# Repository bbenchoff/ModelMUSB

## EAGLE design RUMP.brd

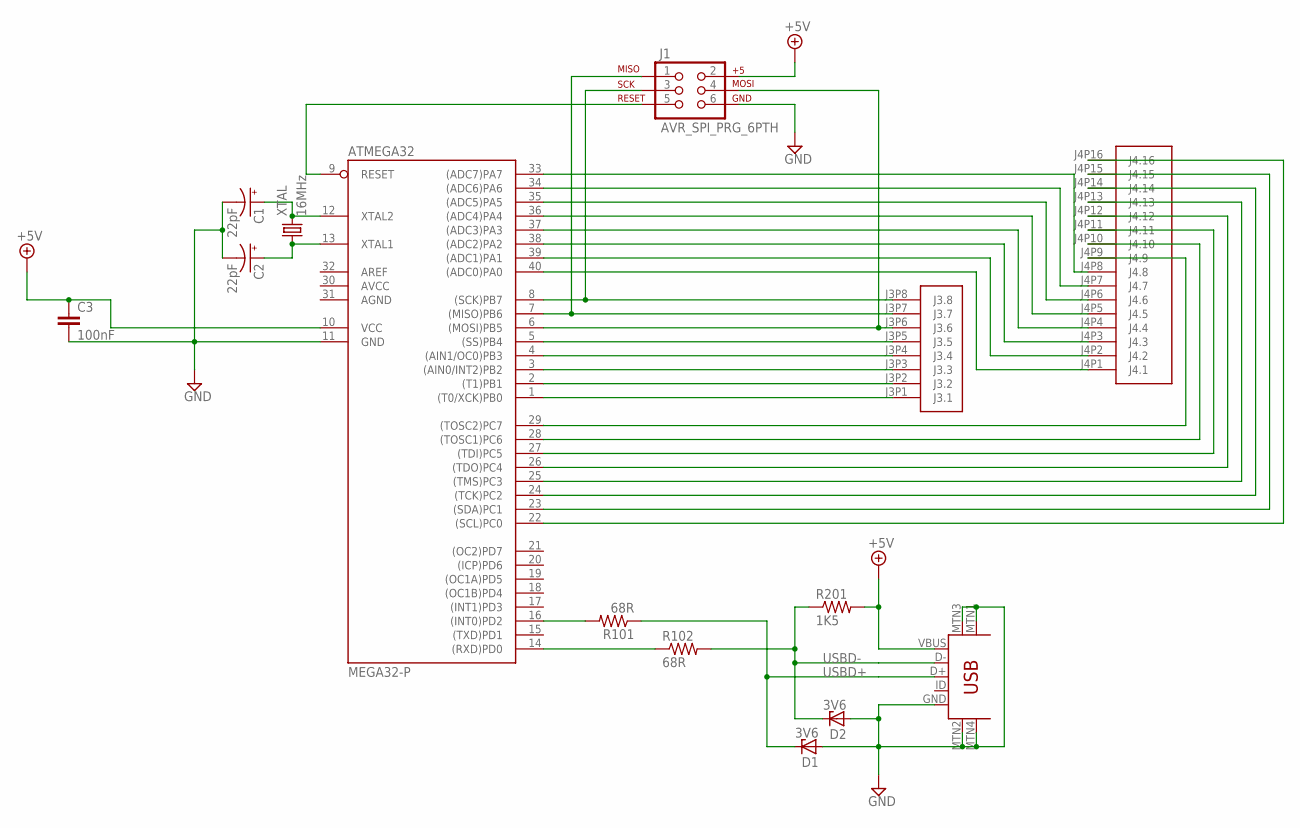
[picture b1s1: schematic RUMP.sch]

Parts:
ATMEGA32: MEGA32-P; DIL40
C1, C2: 22pF; E2-4
C3: 100nF; C2.5-2
D1, D2: 3V6; DO35Z10
J1: AVR_SPI_PRG_6PTH; 2X3
R101, R102: 68R; 0204/7
R201: 1K5; 0204/7
U$1: MODEL-M-J3
U$2: MODEL-M-J4
U$3: USB-MINIB-5PIN; USB-MINIB
XTAL: 16MHz; HC49/S

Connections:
+5V: ATMEGA32.10 (VCC), C3.1, J1.2, R201.2, U$3.VBUS
AGND: ATMEGA32.31 (AGND)
AVCC: ATMEGA32.30 (AVCC)
GND: ATMEGA32.11 (GND), C1.-, C2.-, C3.2, D1.A, D2.A, J1.6, U$3.GND, U$3.MTN1 (MTN2), U$3.MTN2 (MTN3), U$3.MTN3 (MTN1), U$3.MTN4
unnamed: ATMEGA32.14 ((RXD)PD0), R102.1
unnamed: ATMEGA32.16 ((INT0)PD2), R101.2
unnamed: ATMEGA32.1 ((T0/XCK)PB0), U$1.J3P1 (J3.1)
unnamed: ATMEGA32.2 ((T1)PB1), U$1.J3P2 (J3.2)
unnamed: ATMEGA32.3 ((AIN0/INT2)PB2), U$1.J3P3 (J3.3)
unnamed: ATMEGA32.4 ((AIN1/OC0)PB3), U$1.J3P4 (J3.4)
unnamed: ATMEGA32.5 ((SS)PB4), U$1.J3P5 (J3.5)
unnamed: ATMEGA32.6 ((MOSI)PB5), J1.4, U$1.J3P6 (J3.6)
unnamed: ATMEGA32.7 ((MISO)PB6), J1.1, U$1.J3P7 (J3.7)
unnamed: ATMEGA32.8 ((SCK)PB7), J1.3, U$1.J3P8 (J3.8)
unnamed: ATMEGA32.40 ((ADC0)PA0), U$2.J4P1 (J4.1)
unnamed: ATMEGA32.39 ((ADC1)PA1), U$2.J4P2 (J4.2)
unnamed: ATMEGA32.38 ((ADC2)PA2), U$2.J4P3 (J4.3)
unnamed: ATMEGA32.37 ((ADC3)PA3), U$2.J4P4 (J4.4)
unnamed: ATMEGA32.36 ((ADC4)PA4), U$2.J4P5 (J4.5)
unnamed: ATMEGA32.35 ((ADC5)PA5), U$2.J4P6 (J4.6)
unnamed: ATMEGA32.34 ((ADC6)PA6), U$2.J4P7 (J4.7)
unnamed: ATMEGA32.33 ((ADC7)PA7), U$2.J4P8 (J4.8)
unnamed: ATMEGA32.12 (XTAL2), C1.+, XTAL.2
unnamed: ATMEGA32.13 (XTAL1), C2.+, XTAL.1
unnamed: ATMEGA32.29 ((TOSC2)PC7), U$2.J4P9 (J4.9)
unnamed: ATMEGA32.28 ((TOSC1)PC6), U$2.J4P10 (J4.10)
unnamed: ATMEGA32.27 ((TDI)PC5), U$2.J4P11 (J4.11)
unnamed: ATMEGA32.26 ((TDO)PC4), U$2.J4P12 (J4.12)
unnamed: ATMEGA32.25 ((TMS)PC3), U$2.J4P13 (J4.13)
unnamed: ATMEGA32.24 ((TCK)PC2), U$2.J4P14 (J4.14)
unnamed: ATMEGA32.23 ((SDA)PC1), U$2.J4P15 (J4.15)
unnamed: ATMEGA32.22 ((SCL)PC0), U$2.J4P16 (J4.16)
RESET: ATMEGA32.9 (RESET), J1.5
USBD+: D1.C, R101.1, U$3.D+
USBD-: D2.C, R102.2, R201.1, U$3.D-

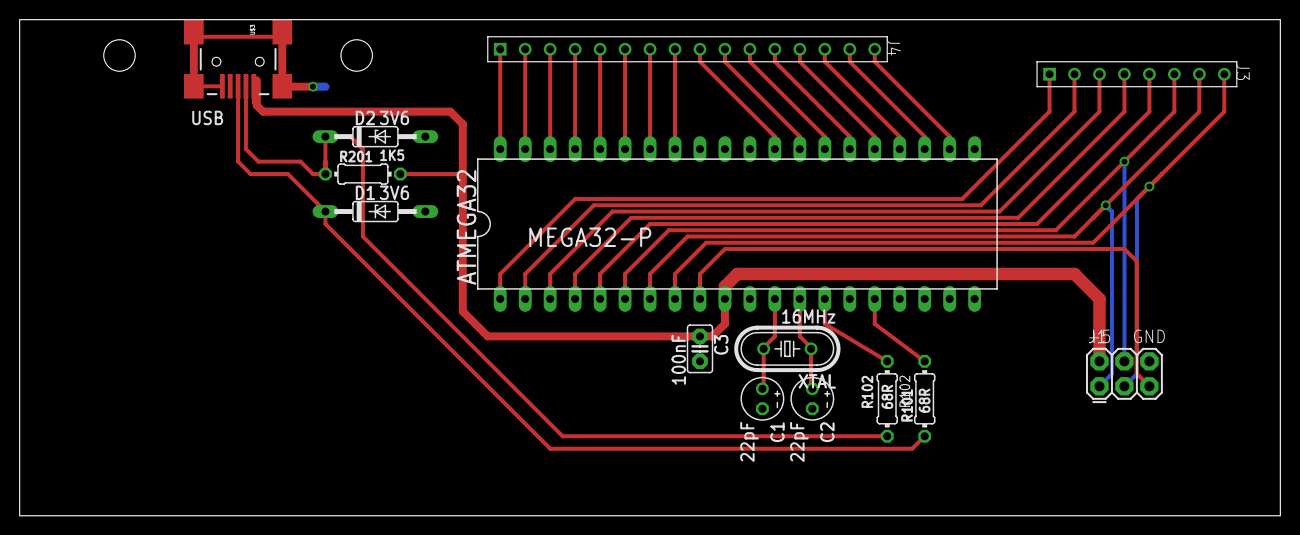
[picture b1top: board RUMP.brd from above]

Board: 2 copper layers, 128.2 x 50.5 mm, 14 parts (0 on the bottom side), 33 nets.

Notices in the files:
parts and their libraries:
SparkFun-Connectors: Licensing: CC v3.0 Share-Alike You are welcome to use this library for commercial purposes.
